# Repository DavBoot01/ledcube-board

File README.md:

# ledcube8x8x8-board

This is a Kicad project for a Led Cube 8x8x8 controller board.

### Tags

- FPGA/CPLD
- ESP32
- Led controller

### Used Library and Footprint

- DigiKey: https://github.com/Digi-Key/digikey-kicad-library
- LM1085: https://app.ultralibrarian.com/details/15DE1302-103F-11E9-AB3A-0A3560A4CCCC/Texas-Instruments/LM1085IS-12-NOPB?ref=digikey
- SN74LVCC3245APWR: https://www.snapeda.com/parts/SN74LVCC3245APWR/TEXAS%20INSTRUMENTS%20(VA)/view-part/?ref=digikey
- B8B-PH-SM4-TB: https://www.snapeda.com/parts/B8B-PH-SM4-TB(LF)(SN)/JST%20Sales/view-part/?ref=digikey
- ESP32-DEVKITC-32D: https://www.snapeda.com/parts/ESP32-DEVKITC-32D/Espressif%20Systems/view-part/
- (SLOT uSD) WM6357CT-ND: https://www.snapeda.com/parts/104031-0811/Molex/view-part/?ref=digikey
- IP4220CZ6F: https://www.snapeda.com/parts/IP4220CZ6/NXP%20Semiconductors/view-part/?ref=digikey

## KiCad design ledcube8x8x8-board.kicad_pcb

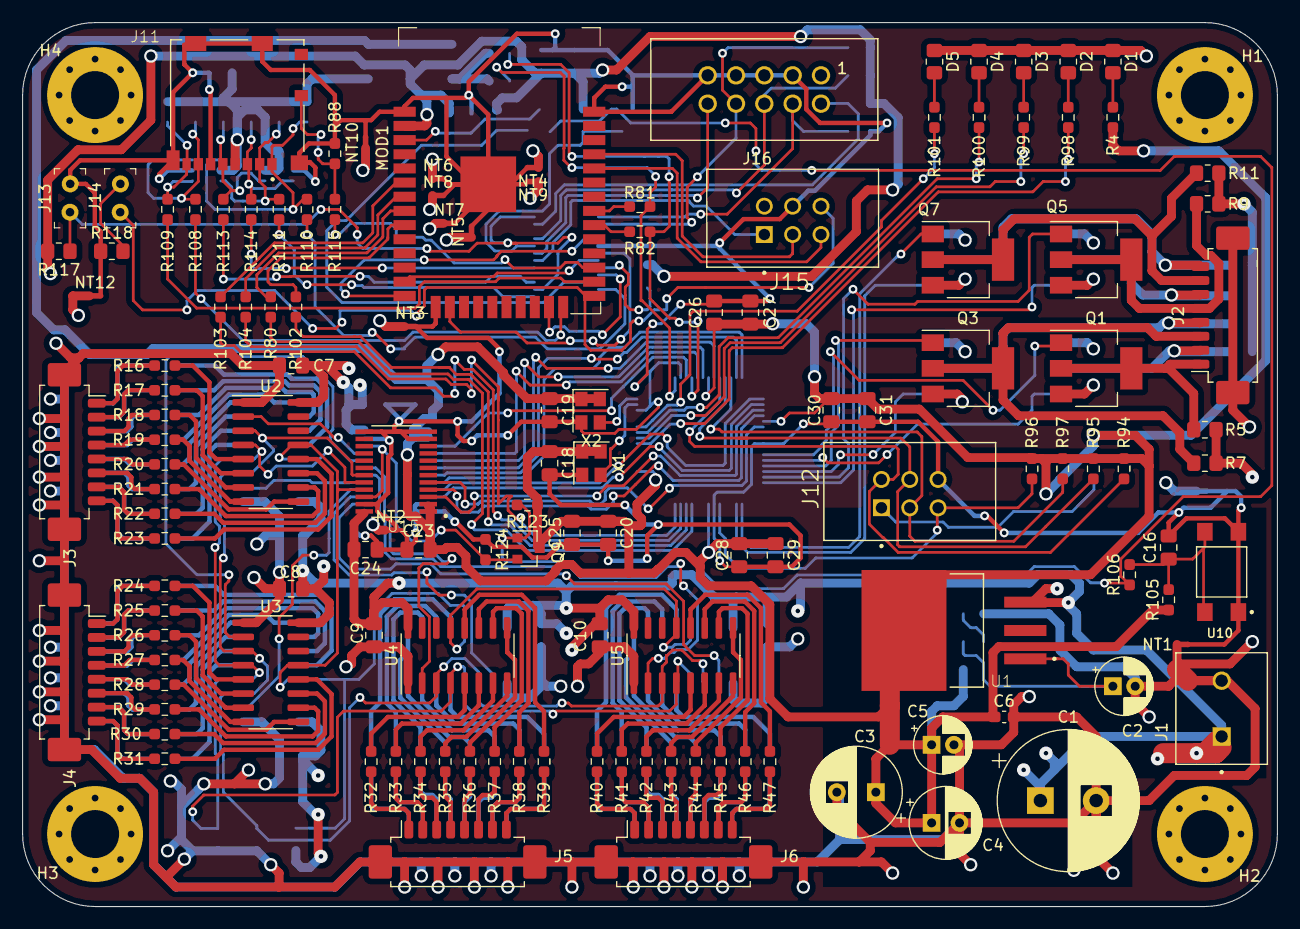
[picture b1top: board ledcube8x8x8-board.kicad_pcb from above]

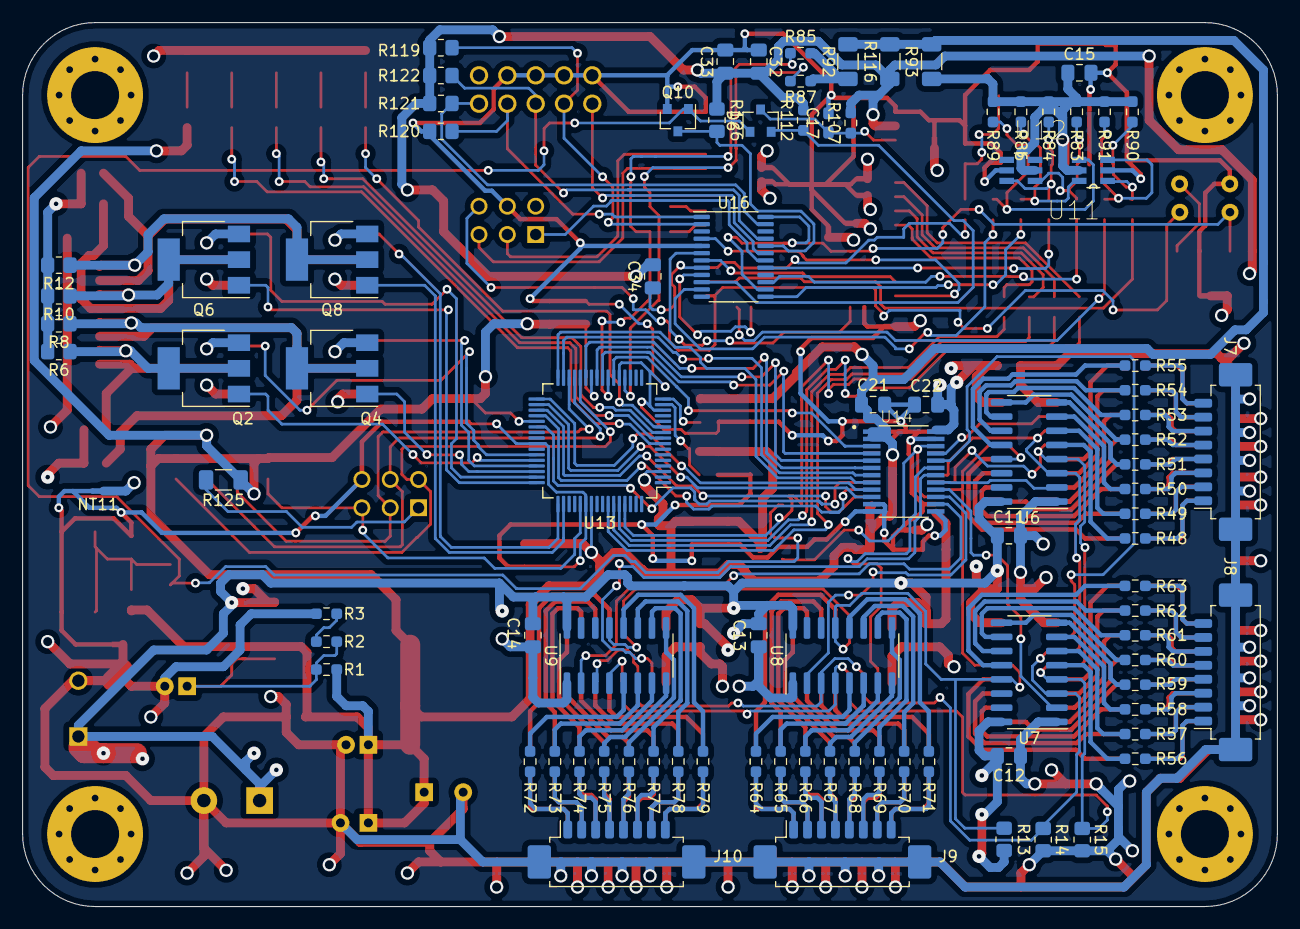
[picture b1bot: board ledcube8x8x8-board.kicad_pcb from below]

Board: 4 copper layers, 112.5 x 79.2 mm, 227 parts (92 on the bottom side), 239 nets.

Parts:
C1: 1000uF; CP_Radial_D12.5mm_P5.00mm
C2, C5: 10uF; CP_Radial_D5.0mm_P2.00mm
C3: 150uF; CP_Radial_D8.0mm_P3.50mm
C4: 100uF; CP_Radial_D6.3mm_P2.50mm
C6, C17: 1uF; C_0603_1608Metric_Pad1.08x0.95mm_HandSolder
C7, C8, C9, C10, C11, C12, C13, C14, C16, C21, C22, C23, C24, C28, C29, C30, C31, C32: 100nF; C_0805_2012Metric_Pad1.18x1.45mm_HandSolder
C15, C34: 4.7uF; C_0805_2012Metric_Pad1.18x1.45mm_HandSolder
C18, C19, C20, C25, C26, C27: 10nF; C_0805_2012Metric_Pad1.18x1.45mm_HandSolder
C33: 22uF; C_0805_2012Metric_Pad1.18x1.45mm_HandSolder
D1, D3: GREEN; R_0805_2012Metric_Pad1.20x1.40mm_HandSolder
D2: RED; R_0805_2012Metric_Pad1.20x1.40mm_HandSolder
D4, D5: ORANGE; R_0805_2012Metric_Pad1.20x1.40mm_HandSolder
D6: BAT54A; SOT-23
H1, H2, H3, H4: MountingHole_Pad; MountingHole_4.3mm_M4_Pad_Via
J1: 282836-2; CONN_282836-2
J2, J3, J4, J5, J6, J7, J8, J9, J10: molex_53261-0871; Molex_PicoBlade_53261-0871_1x08-1MP_P1.25mm_Horizontal
J11: 104031-0811; MOLEX_104031-0811
J12, J15: 30306-6002HB; 3M_30306-6002HB
J13, J14: hedear; PinHeader_1x2_P2.54mm
J16: 61201021621
MOD1: ESP32-WROOM-32; ESP32-WROOM-32D
NT1, NT2, NT3, NT4, NT5, NT6, NT7, NT8, NT9, NT10, NT11, NT12: Net-Tie_2; NetTie-2_SMD_Pad0.5mm
Q1, Q2, Q3, Q4, Q5, Q6, Q7, Q8: Q_NMOS_GDSD; SOT-223
Q9, Q10: Q_PMOS_GSD; SOT-23
R1: 121; R_0603_1608Metric_Pad0.98x0.95mm_HandSolder
R2: 42.2; R_0603_1608Metric_Pad0.98x0.95mm_HandSolder
R3: 56.2; R_0603_1608Metric_Pad0.98x0.95mm_HandSolder
R4, R98, R99, R100, R101: 1K; R_0603_1608Metric_Pad0.98x0.95mm_HandSolder
R5, R6, R7, R8, R9, R10, R11, R12, R13, R14, R15, R117, R118, R119, R120, R121, R122, R126: 10K; R_0805_2012Metric_Pad1.20x1.40mm_HandSolder
R16, R17, R18, R19, R20, R21, R22, R23, R24, R25, R26, R27, R28, R29, R30, R31, R32, R33, R34, R35, R36, R37, R38, R39, R40, R41, R42, R43, R44, R45, R46, R47, R48, R49, R50, R51, R52, R53, R54, R55, R56, R57, R58, R59, R60, R61, R62, R63, R64, R65, R66, R67, R68, R69, R70, R71, R72, R73, R74, R75, R76, R77, R78, R79: 100; R_0603_1608Metric_Pad0.98x0.95mm_HandSolder
R80, R81, R82, R102, R103, R104, R106, R108, R109, R110, R111, R113, R114, R115: 0R; R_0603_1608Metric_Pad0.98x0.95mm_HandSolder
R83, R84, R86, R88, R89, R90, R91, R94, R95, R96, R97, R105, R107, R123, R124: 10K; R_0603_1608Metric_Pad0.98x0.95mm_HandSolder
R85, R87: 2K7; R_0603_1608Metric_Pad0.98x0.95mm_HandSolder
R92, R93, R116, R125: 0R; R_1206_3216Metric_Pad1.30x1.75mm_HandSolder
R112: 47K; R_0603_1608Metric_Pad0.98x0.95mm_HandSolder
U1: LM1085IS-12; TO254P1524X483-4N
U2, U3, U4, U5, U6, U7, U8, U9: STP08CP05MTR; SOIC-16_3.9x9.9mm_P1.27mm
U10: TL3305AF260QG; SW_TL3305AF260QG
U11, U12: IP4220CZ6; SOT95P275X110-6N
U13: XC9572XL-VQ64; TQFP-64_10x10mm_P0.5mm
U14, U15: SN74LVCC3245APWR; SOP65P640X120-24N
U16: TS3A27518EPW; TSSOP-24_4.4x7.8mm_P0.65mm
X1: ASE-40MHz; Oscillator_SMD_Abracon_ASE-4Pin_3.2x2.5mm
X2: ASE-25MHz; Oscillator_SMD_Abracon_ASE-4Pin_3.2x2.5mm

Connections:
/DATA_LED1: U2.2, U14.21
/DATA_LED2: U3.2, U14.20
/DATA_LED3: U4.2, U14.19
/DATA_LED4: U5.2, U14.18
/DATA_LED5: U6.2, U14.17
/DATA_LED6: U7.2, U14.16
/DATA_LED7: U8.2, U14.15
/DATA_LED8: U9.2, U14.14
/LAYER_SEL1: Q1.1, U13.43
/LAYER_SEL2: Q2.1, U13.44
/LAYER_SEL3: Q3.1, U13.45
/LAYER_SEL4: Q4.1, U13.46
/LAYER_SEL5: Q5.1, U13.47
/LAYER_SEL6: Q6.1, U13.48
/LAYER_SEL7: Q7.1, U13.49
/LAYER_SEL8: Q8.1, U13.50
/VCC_3V3: C3.1, C4.1, C5.1, C6.1, C18.1, C19.1, C20.1, C21.2, C23.2, C25.1, C26.1, C27.1, C28.1, C29.1, C30.1, C31.1, Q9.3, R1.1, R4.1, R92.2, R93.2, R94.1, R95.1, R96.1, R97.1, R105.1, R116.2, R123.1, R125.1, U1.4, U13.3, U13.26, U13.37, U13.55, U14.1, U14.2, U15.1, U15.2, X1.1, X1.4, X2.1, X2.4
/VCC_5V0: C1.1, C7.1, C8.1, C9.1, C10.1, C11.1, C12.1, C13.1, C14.1, C22.2, C24.2, J1.1, R5.2, R6.2, R7.2, R8.2, R9.2, R10.2, R11.2, R12.2, R13.1, U1.3, U2.16, U3.16, U4.16, U5.16, U6.16, U7.16, U8.16, U9.16, U14.24, U15.24
/layer_led_mux.sch/CLK: R14.1, U2.3, U3.3, U4.3, U5.3, U6.3, U7.3, U8.3, U9.3, U15.19
/layer_selector.sch/LAYER_SEL1: J2.1, Q1.2, Q1.4, R5.1
/layer_selector.sch/LAYER_SEL2: J2.2, Q2.2, Q2.4, R6.1
/layer_selector.sch/LAYER_SEL3: J2.3, Q3.2, Q3.4, R7.1
/layer_selector.sch/LAYER_SEL4: J2.4, Q4.2, Q4.4, R8.1
/layer_selector.sch/LAYER_SEL5: J2.5, Q5.2, Q5.4, R9.1
/layer_selector.sch/LAYER_SEL6: J2.6, Q6.2, Q6.4, R10.1
/layer_selector.sch/LAYER_SEL7: J2.7, Q7.2, Q7.4, R11.1
/layer_selector.sch/LAYER_SEL8: J2.8, Q8.2, Q8.4, R12.1
/pl.sch/CLK_25M: U13.16, X2.3
/pl.sch/CLK_40M: U13.15, X1.3
/pl.sch/DATA_CLK_3V3: U13.38, U15.5
/pl.sch/DATA_LE_3V3: U13.36, U15.4
/pl.sch/DATA_LE_5V0: R15.1, U2.4, U3.4, U4.4, U5.4, U6.4, U7.4, U8.4, U9.4, U15.20
/pl.sch/DATA_ROW1_3V3: U13.22, U14.3
/pl.sch/DATA_ROW2_3V3: U13.24, U14.4
/pl.sch/DATA_ROW3_3V3: U13.25, U14.5
/pl.sch/DATA_ROW4_3V3: U13.27, U14.6
/pl.sch/DATA_ROW5_3V3: U13.31, U14.7
/pl.sch/DATA_ROW6_3V3: U13.32, U14.8
/pl.sch/DATA_ROW7_3V3: U13.33, U14.9
/pl.sch/DATA_ROW8_3V3: U13.34, U14.10
/pl.sch/GPIO0: R80.1, U13.58
/pl.sch/GPIO1: R102.1, U13.59
/pl.sch/GPIO2: R103.1, U13.60
/pl.sch/GPIO3: R104.1, U13.61
/pl.sch/I2C_SCL: R81.1, R87.2, U13.20
/pl.sch/I2C_SDA: R82.1, R85.2, U13.23
/pl.sch/LED_G: R99.1, U13.9
/pl.sch/LED_O1: R100.1, U13.10
/pl.sch/LED_O2: R101.1, U13.11
/pl.sch/LED_R: R98.1, U13.8
/pl.sch/TCK: J12.3, R97.2, U13.30
/pl.sch/TDI: J12.2, R94.2, U13.28
/pl.sch/TDO: J12.5, R96.2, U13.53
/pl.sch/TMS: J12.4, R95.2, U13.29
/pl.sch/~DATA_OE_3V3: U13.35, U15.3
/pl.sch/~DATA_OE_5V0: R13.2, U2.13, U3.13, U4.13, U5.13, U6.13, U7.13, U8.13, U9.13, U15.21
/pl.sch/~OE: Q9.2, R124.1, U14.22, U15.22
/pl.sch/~SYS_RST: D6.1, Q9.1, Q10.1, R106.1, R123.2
/ps.sch/ESP_GPIO0: MOD1.8, R80.2
/ps.sch/ESP_GPIO1: MOD1.9, R102.2
/ps.sch/ESP_GPIO2: MOD1.6, R103.2
/ps.sch/ESP_GPIO3: MOD1.7, R104.2
/ps.sch/ESP_I2C_SCL: MOD1.31, R81.2
/ps.sch/ESP_I2C_SDA: MOD1.30, R82.2
/ps.sch/ESP_PU: C17.1, D6.3, MOD1.3, R107.2
/ps.sch/GPIO0: J14.1, J15.6, MOD1.25
/ps.sch/MTCK_SDDATA3: MOD1.16, U16.6
/ps.sch/MTDI_SDDATA2: MOD1.14, U16.4
/ps.sch/MTDO_SDCMD: MOD1.23, U16.9
/ps.sch/MTMS_SDCLK: MOD1.13, U16.7
/ps.sch/MUX_SEL_PRG: J13.1, R117.1, U16.14, U16.24
/ps.sch/PREST: J15.1, U16.18
/ps.sch/PRG_REST: D6.2, R112.2, U16.10
/ps.sch/R_nTRST: J16.10, U16.19
/ps.sch/SDDATA0: MOD1.24, R108.2
/ps.sch/SDDATA1: MOD1.26, R109.2
/ps.sch/SD_CD: MOD1.27, R115.1
/ps.sch/SD_CLK: R113.1, U16.15
/ps.sch/SD_CMD: R114.1, U16.17
/ps.sch/SD_DAT2: R110.2, U16.11
/ps.sch/SD_DAT3: R111.2, U16.13
/ps.sch/TCK: J16.4, R120.2, U16.1
/ps.sch/TDI: J16.8, R119.2, U16.2
/ps.sch/TDO: J16.6, R122.2, U16.21
/ps.sch/TMS: J16.2, R121.2, U16.23
/ps.sch/U0RXD: J15.5, MOD1.34
/ps.sch/U0TXD: J15.3, MOD1.35
ESP_3V3: C32.1, C33.1, C34.2, MOD1.2, R107.1, R112.1, R116.1, R117.2, R119.1, R121.1, R122.1, R126.2
GND: C1.2, C2.2, C3.2, C4.2, C5.2, C6.2, C7.2, C8.2, C9.2, C10.2, C11.2, C12.2, C13.2, C14.2, D1.1, D2.1, D3.1, D4.1, D5.1, H1.1, H2.1, H3.1, H4.1, J1.2, J2.MP, J3.MP, J4.MP, J5.MP, J6.MP, J7.MP, J8.MP, J9.MP, J10.MP, NT1.1, NT2.1, NT3.1, NT4.1, NT5.1, NT6.1, NT7.1, NT8.1, NT9.1, NT10.1, NT11.1, NT12.1, Q1.3, Q2.3, Q3.3, Q4.3, Q5.3, Q6.3, Q7.3, Q8.3, R3.2, R14.2, R15.2, U2.1, U3.1, U4.1, U5.1, U6.1, U7.1, U8.1, U9.1
GNDD: C15.2, C16.2, C17.2, C18.2, C19.2, C20.2, C21.1, C22.1, C23.1, C24.1, C25.2, C26.2, C27.2, C28.2, C29.2, C30.2, C31.2, C32.2, C33.2, J11.6, J11.G1, J11.G2, J11.G3, J11.G4, J12.6, J13.2, J15.4, J16.3, J16.5, J16.7, J16.9, MOD1.1, MOD1.15, MOD1.38, MOD1.39, NT1.2, NT2.2, NT3.2, NT4.2, NT5.2, NT6.2, NT7.2, NT8.2, NT9.2, NT10.2, NT11.2, NT12.2, Q10.2, R88.2, R118.1, R120.1, R124.2, U10.1, U10.2, U11.2, U12.2, U13.14, U13.21, U13.41, U13.54, U14.11, U14.12, U14.13, U14.23, U15.11, U15.12, U15.13, U15.23, U16.5, X1.2, X2.2
I2C_3V3: R85.1, R87.1, R92.1
unnamed: C2.1, R1.2, R2.1, U1.1
unnamed: C16.1, R105.2, R106.2, U10.3, U10.4
unnamed: C34.1, U16.8
unnamed: D1.2, R4.2
unnamed: D2.2, R98.2
unnamed: D3.2, R99.2
unnamed: D4.2, R100.2
unnamed: D5.2, R101.2
unnamed: J3.1, R16.1
unnamed: J3.2, R17.1
unnamed: J3.3, R18.1
unnamed: J3.4, R19.1
unnamed: J3.5, R20.1
unnamed: J3.6, R21.1
unnamed: J3.7, R22.1
unnamed: J3.8, R23.1
unnamed: J4.1, R24.1
unnamed: J4.2, R25.1
unnamed: J4.3, R26.1
unnamed: J4.4, R27.1
unnamed: J4.5, R28.1
unnamed: J4.6, R29.1
unnamed: J4.7, R30.1
unnamed: J4.8, R31.1
unnamed: J5.1, R32.1
unnamed: J5.2, R33.1
unnamed: J5.3, R34.1
unnamed: J5.4, R35.1
unnamed: J5.5, R36.1
unnamed: J5.6, R37.1
unnamed: J5.7, R38.1
unnamed: J5.8, R39.1
unnamed: J6.1, R40.1
unnamed: J6.2, R41.1
unnamed: J6.3, R42.1
unnamed: J6.4, R43.1
unnamed: J6.5, R44.1
unnamed: J6.6, R45.1
unnamed: J6.7, R46.1
unnamed: J6.8, R47.1
unnamed: J7.1, R48.1
unnamed: J7.2, R49.1
unnamed: J7.3, R50.1
unnamed: J7.4, R51.1
unnamed: J7.5, R52.1
unnamed: J7.6, R53.1
unnamed: J7.7, R54.1
unnamed: J7.8, R55.1
unnamed: J8.1, R56.1
unnamed: J8.2, R57.1
unnamed: J8.3, R58.1
unnamed: J8.4, R59.1
unnamed: J8.5, R60.1
unnamed: J8.6, R61.1
unnamed: J8.7, R62.1
unnamed: J8.8, R63.1
unnamed: J9.1, R64.1
unnamed: J9.2, R65.1
unnamed: J9.3, R66.1
unnamed: J9.4, R67.1
unnamed: J9.5, R68.1
unnamed: J9.6, R69.1
unnamed: J9.7, R70.1
unnamed: J9.8, R71.1
unnamed: J10.1, R72.1
unnamed: J10.2, R73.1
unnamed: J10.3, R74.1
unnamed: J10.4, R75.1
unnamed: J10.5, R76.1
unnamed: J10.6, R77.1
unnamed: J10.7, R78.1
unnamed: J10.8, R79.1
unnamed: J11.1, R89.2, R110.1, U11.4
unnamed: J11.2, R86.2, R111.1, U11.6
unnamed: J11.3, R84.2, R114.2, U12.3
unnamed: J11.5, R83.2, R113.2, U12.4
unnamed: J11.7, R91.2, R108.1, U11.3
unnamed: J11.8, R90.2, R109.1, U11.1
unnamed: J11.9, R88.1, R115.2
unnamed: J12.1, R125.2
unnamed: J14.2, R118.2
unnamed: Q10.3, R126.1, U16.20
unnamed: R2.2, R3.1
unnamed: R16.2, U2.5
unnamed: R17.2, U2.6
unnamed: R18.2, U2.7
unnamed: R19.2, U2.8
unnamed: R20.2, U2.9
unnamed: R21.2, U2.10
unnamed: R22.2, U2.11
unnamed: R23.2, U2.12
unnamed: R24.2, U3.5
unnamed: R25.2, U3.6
unnamed: R26.2, U3.7
unnamed: R27.2, U3.8
unnamed: R28.2, U3.9
unnamed: R29.2, U3.10
unnamed: R30.2, U3.11
unnamed: R31.2, U3.12
unnamed: R32.2, U4.5
unnamed: R33.2, U4.6
unnamed: R34.2, U4.7
unnamed: R35.2, U4.8
unnamed: R36.2, U4.9
unnamed: R37.2, U4.10
unnamed: R38.2, U4.11
unnamed: R39.2, U4.12
unnamed: R40.2, U5.5
unnamed: R41.2, U5.6
unnamed: R42.2, U5.7
unnamed: R43.2, U5.8
unnamed: R44.2, U5.9
unnamed: R45.2, U5.10
unnamed: R46.2, U5.11
unnamed: R47.2, U5.12
unnamed: R48.2, U6.5
unnamed: R49.2, U6.6
unnamed: R50.2, U6.7
unnamed: R51.2, U6.8
unnamed: R52.2, U6.9
unnamed: R53.2, U6.10
unnamed: R54.2, U6.11
unnamed: R55.2, U6.12
unnamed: R56.2, U7.5
unnamed: R57.2, U7.6
unnamed: R58.2, U7.7
unnamed: R59.2, U7.8
unnamed: R60.2, U7.9
unnamed: R61.2, U7.10
unnamed: R62.2, U7.11
unnamed: R63.2, U7.12
unnamed: R64.2, U8.5
unnamed: R65.2, U8.6
unnamed: R66.2, U8.7
unnamed: R67.2, U8.8
unnamed: R68.2, U8.9
unnamed: R69.2, U8.10
unnamed: R70.2, U8.11
unnamed: R71.2, U8.12
unnamed: R72.2, U9.5
unnamed: R73.2, U9.6
unnamed: R74.2, U9.7
unnamed: R75.2, U9.8
unnamed: R76.2, U9.9
unnamed: R77.2, U9.10
unnamed: R78.2, U9.11
unnamed: R79.2, U9.12
SD_3V3: C15.1, J11.4, R83.1, R84.1, R86.1, R89.1, R90.1, R91.1, R93.1, U11.5, U12.5

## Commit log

2021-04-05 KiCad empty project
2021-04-05 Add power supply schematic part
    Input: 5V
    Output: 3.3V
    Used a PMIC Lineary regulator voltage (LM1085IS)
2021-04-06 Add programmable logic (pl) schematic part
    Use a Xilinx's CPLD: XC9572XL-VQ64
    The board provides:
    - JTAG interface for this CPLD;
    - two CPLD's input source clocks @ 40MHz and 25MHz.
    Main function: Manage all signals of the cube, included the timing.
2021-04-06 Add layer selector schematic part
    Main function: is a common sink for the GND for all layers of the
    cube. Is like a multiplexer that the PL part drives properly so
    that only one layer at a time is connected to GND.
2021-04-06 Add layer led muxing schematic part
    Main funcion: also this part is driven by the CPLD. This part of
    schematic has 64 output (one for each led of each layers - to
    remember that all leds in a single column are connect togheter
    through the anode - ). In this way all 64 leds can be driven
    with 11 signal from CPLD (8 for data and 3 for control) instead of
    64.
2021-04-06 Add microcontroller (ps) schematic part
    This part is compatible with the external board ESP32-DEVKITC-32D.
    The ESP32 microcontroller is connected to CPLD via I2C bus and some
    other GPIOs signal. Moreover, on board there is also a uSD card slot
    connected to the ESP32.
    External reference:
    - https://docs.espressif.com/projects/esp-idf/en/latest/esp32/hw-reference/esp32/get-started-devkitc.html
2021-04-06 Update README.md
    Add reference about library/footprint used for PS schematic part
2021-04-07 Export of all pin sheet
2021-04-07 Connect all macro blocks
2021-04-07 Fix bug on bus's linking
2021-04-07 Remove resistor on 3.3V of ESP connector in order to avoid a warning
2021-04-07 Add four mounting hole pads
2021-04-08 Add four GPIOs between PL and PS
2021-04-17 Chage vertical connector with molex horizontal connector
2021-04-17 Update schematic with newest molex connector into external library
2021-04-17 PCB: relative placement of connectors for row maagement
2021-04-17 PCB: routing for connectors J3...J10
2021-04-18 Complete routing of single part of led connectors
2021-04-18 Schematic: Change uSD connector (now is a Molex one)
2021-04-18 Schematic: Fix connection error
2021-04-20 PCB: partial routing of CPLD part
2021-04-22 PCB: Placement of all top layer
2021-04-22 PCB: Resize of some net of layer selector part
2021-04-24 PCB: Placement @ 95%
2021-04-24 Change footprint from 0805 to 1206 of resistors that connect I2C_3V3 and SD_3V3 to source
2021-04-24 Chnage line for SD protection
2021-04-24 Connect SD_CD to IO5 of ESP32
2021-04-24 PCB: Placement @ 98%
2021-04-25 PCB: Place all components
2021-05-02 PCB: complete placement
2021-06-06 Complete PCB placement and routing
2021-07-02 Update PCB traces
2021-08-07 Renamed projet into ledcube8x8x8-board
2021-08-07 Remove old file
2021-08-07 Change PL part: replaced ESP32 DevKit socket with ESP32 module
    The idea is to use directly the ESP32 without any addon or
    extra module to plug on the ledcube board. In this way the board
    is complete itself.
    Also a global reset button has been placed.
2021-08-08 Update footprints
2021-08-08 Start with newest PCB routing
2021-08-08 Relative placement of layer multiplexing
2021-08-09 CHange CPLD's JTAG connector with a pin header
2021-08-09 Change power connector with a Wire-to-Board one
2021-08-09 Change C1,C2,C3,C4,C5 capatictors with a THT type
2021-08-09 Correct some net's labels
2021-08-09 Fix net of CMD/CLD signal of uSD of PS
2021-08-09 Fix power rail of uSD card reader
2021-08-11 PCB: Place some macro blocks
2021-08-13 Place whole PS part. Start with PL one.
2021-08-13 PCB: Re-work routing of led multiplexer part
2021-08-14 PCB: Re-work routing of PS part (now complete)
2021-08-14 PCB: Place led layer multiplexer
2021-09-14 PCB complete
